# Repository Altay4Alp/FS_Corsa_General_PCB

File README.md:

# Formula Student Corsa Node Board
This is a pcb design for a car we made called Corsa. Corsa is made to create experiences for team to make better cars for formula student races. In this pcb design it is aimed to control the car and getting datas from the car. 

The board designed to use: 
- 3 temprature sensor
- 2 servo motor
- 1 dc motor
- 1 gps sensor
- 1 acceleration sensor
- 1 stop light
- 1 can bus line

That list can be used as a default by just programming. But it is designed to be able to use all of the potential of STM32 blue pill. Sensors and other things can be added as wanted.

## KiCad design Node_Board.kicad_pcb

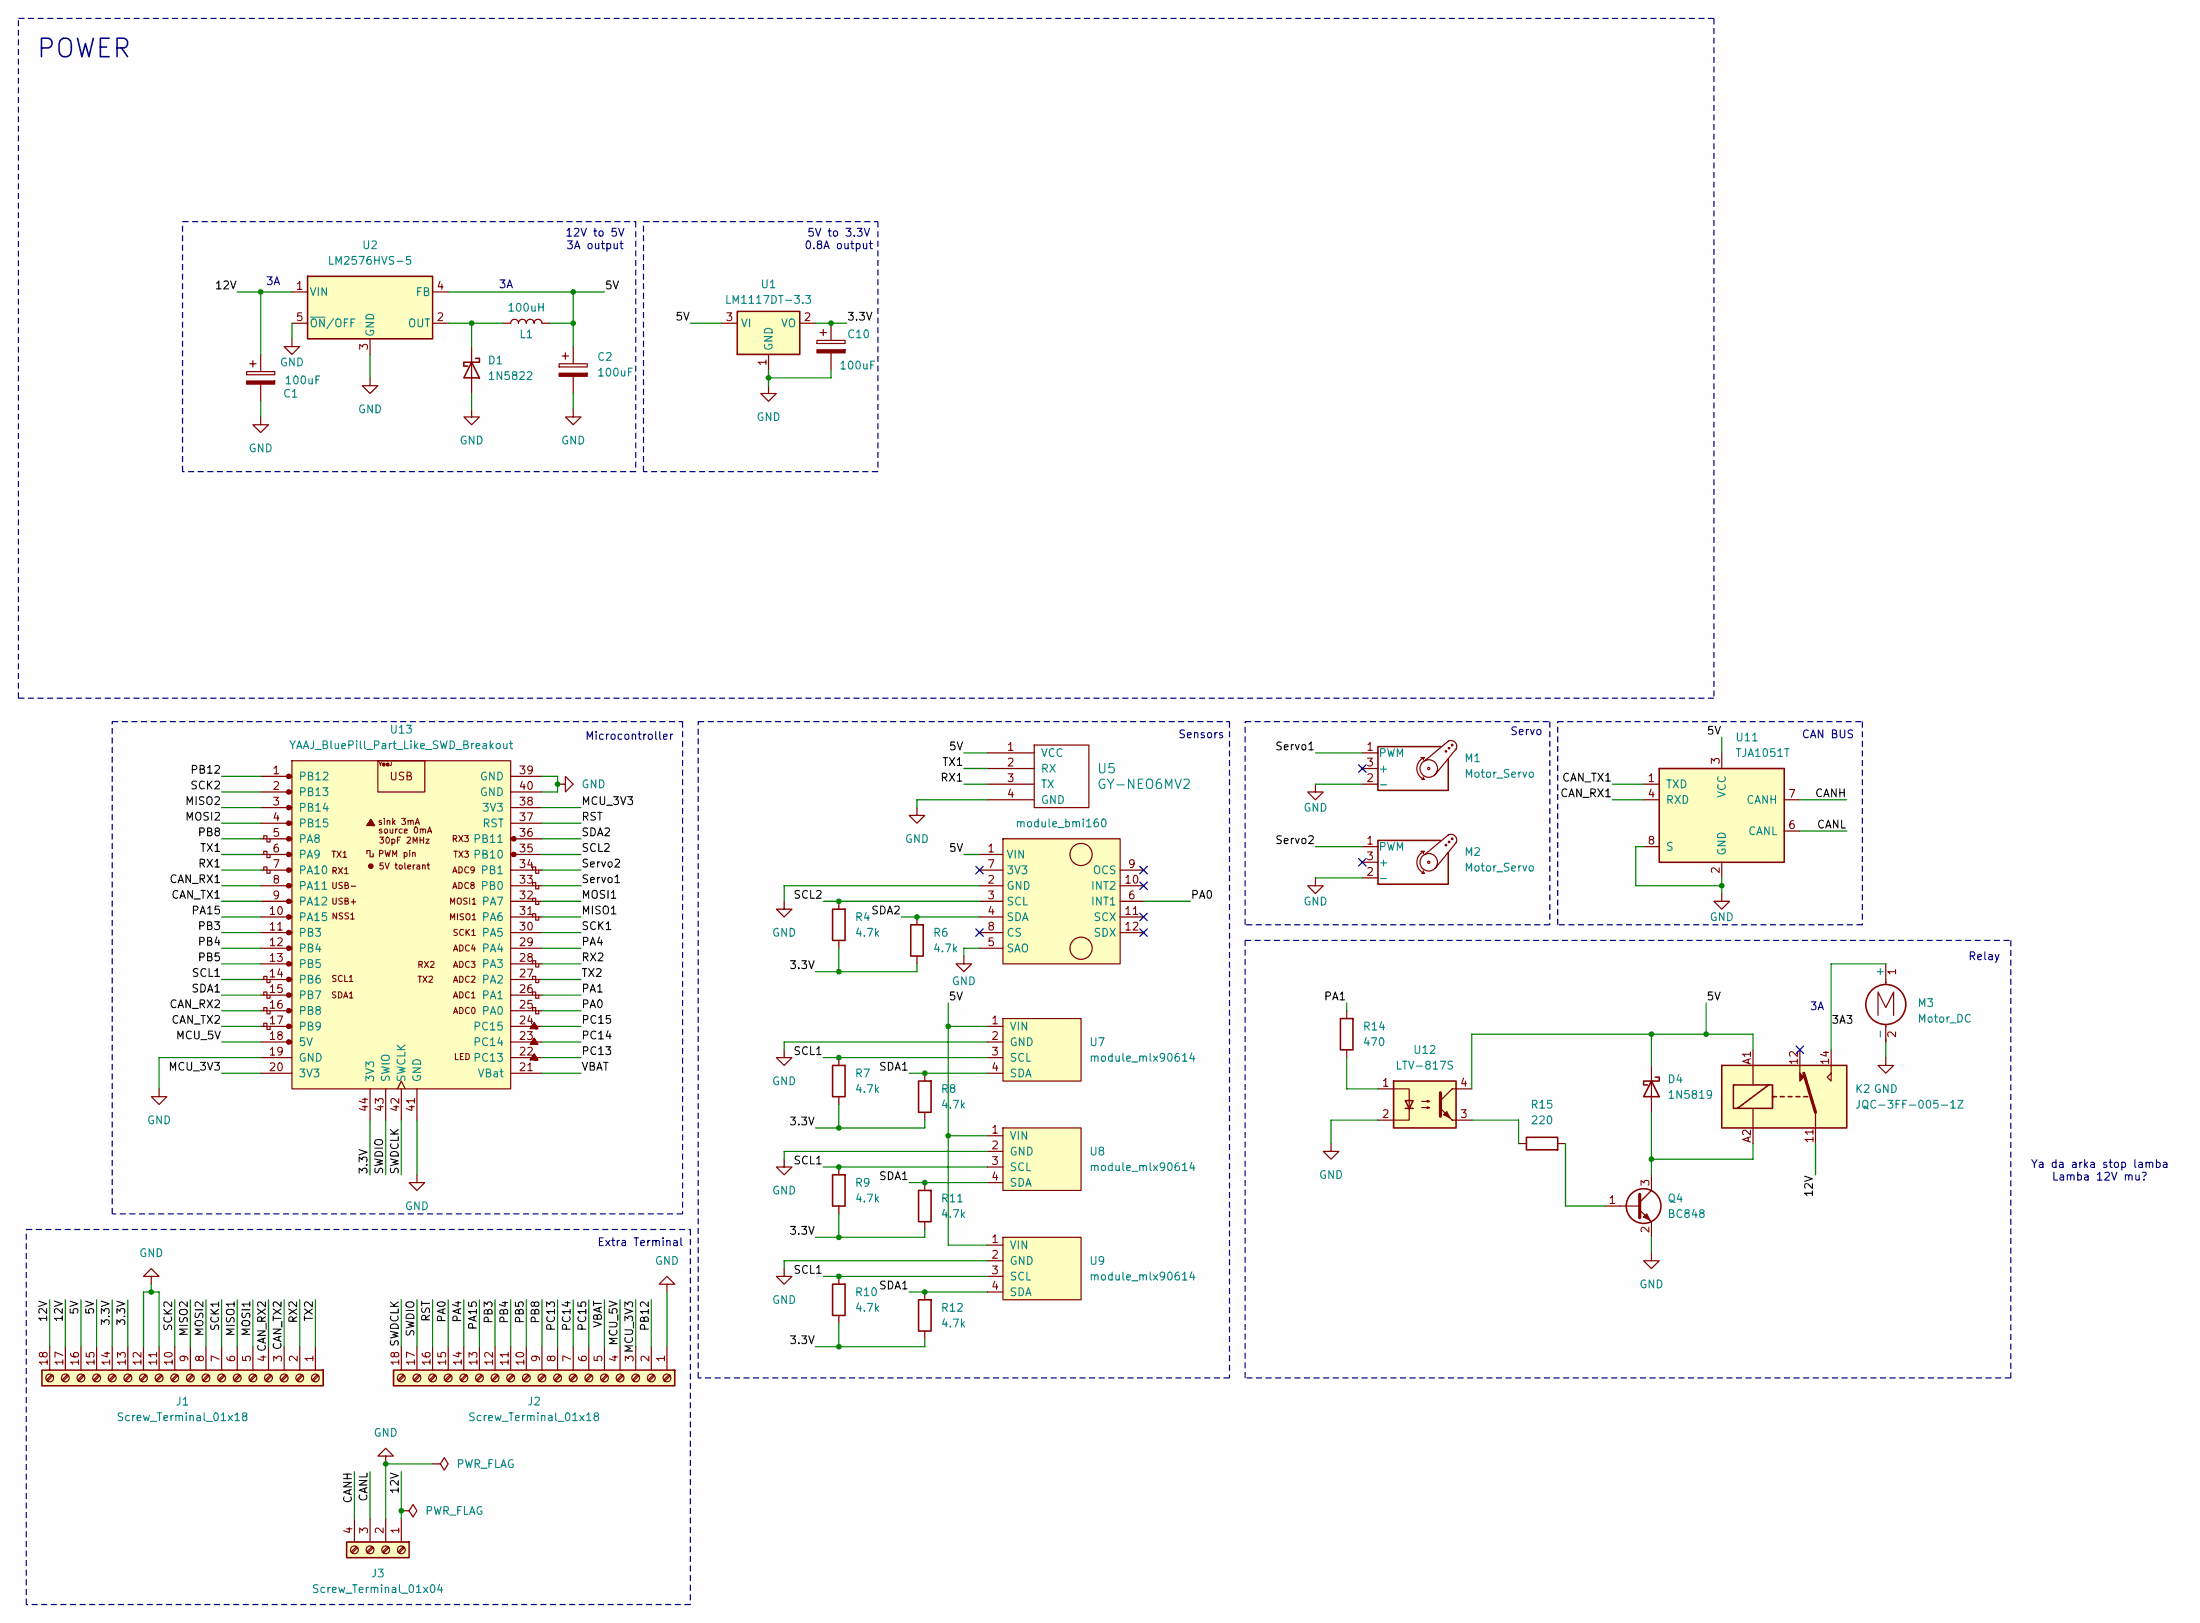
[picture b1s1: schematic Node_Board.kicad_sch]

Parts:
C1, C2: 100uF; CP_Elec_8x10
C10: 100uF; CP_EIA-3528-21_Kemet-B
D1: 1N5822; D_DO-201AD_P15.24mm_Horizontal
D4: 1N5819; D_DO-41_SOD81_P10.16mm_Horizontal
J1, J2: Screw_Terminal_01x18; PinHeader_1x18_P2.54mm_Vertical
J3: Screw_Terminal_01x04; PinHeader_1x04_P2.54mm_Vertical
K2: JQC-3FF-005-1Z; Relay_SPDT_Hongfa_JQC-3FF_0XX-1Z
L1: 100uH; L_12x12mm_H8mm
M1, M2: Motor_Servo; PinHeader_1x02_P2.54mm_Vertical
M3: Motor_DC; PinHeader_1x02_P2.54mm_Vertical
Q4: BC848; SOT-23
R4, R6, R7, R8, R9, R10, R11, R12: 4.7k; R_1206_3216Metric
R14: 470; R_1206_3216Metric
R15: 220; R_1206_3216Metric
U1: LM1117DT-3.3; TO-252-3_TabPin2
U2: LM2576HVS-5; TO-263-5_TabPin3
U5: GY-NEO6MV2; PinHeader_1x04_P2.54mm_Vertical
U7, U8, U9: module_mlx90614; PinHeader_1x04_P2.54mm_Vertical
U10: module_bmi160; PinHeader_1x06_P2.54mm_Vertical
U11: TJA1051T; SOIC-8_3.9x4.9mm_P1.27mm
U12: LTV-817S; SMDIP-4_W9.53mm
U13: YAAJ_BluePill_Part_Like_SWD_Breakout; YAAJ_BluePill_SWD_1

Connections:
/3.3V: C10.1, J1.13, J1.14, R4.1, R6.1, R7.1, R8.1, R9.1, R10.1, R11.1, R12.1, U1.2 (VO), U13.44 (3V3)
/3A3: K2.14, M3.1 (+)
/5V: C2.1, D4.1 (K), J1.15, J1.16, K2.A1, L1.2, U1.3 (VI), U2.4 (FB), U5.1 (VCC), U7.1 (VIN), U8.1 (VIN), U9.1 (VIN), U10.1 (VIN), U11.3 (VCC), U12.4
/12V: C1.1, J1.17, J1.18, J3.1, K2.11, U2.1 (VIN)
/CANH: J3.4, U11.7 (CANH)
/CANL: J3.3, U11.6 (CANL)
/CAN_RX1: U11.4 (RXD), U13.8 (PA11)
/CAN_RX2: J1.4, U13.16 (PB8)
/CAN_TX1: U11.1 (TXD), U13.9 (PA12)
/CAN_TX2: J1.3, U13.17 (PB9)
/MCU_3V3: J2.3, U13.20 (3V3), U13.38 (3V3)
/MCU_5V: J2.4, U13.18 (5V)
/MISO1: J1.6, U13.31 (PA6)
/MISO2: J1.9, U13.3 (PB14)
/MOSI1: J1.5, U13.32 (PA7)
/MOSI2: J1.8, U13.4 (PB15)
/PA0: J2.15, U10.6 (INT1), U13.25 (PA0)
/PA1: R14.2, U13.26 (PA1)
/PA4: J2.14, U13.29 (PA4)
/PA15: J2.13, U13.10 (PA15)
/PB3: J2.12, U13.11 (PB3)
/PB4: J2.11, U13.12 (PB4)
/PB5: J2.10, U13.13 (PB5)
/PB8: J2.9, U13.5 (PA8)
/PB12: J2.2, U13.1 (PB12)
/PC13: J2.8, U13.22 (PC13)
/PC14: J2.7, U13.23 (PC14)
/PC15: J2.6, U13.24 (PC15)
/RST: J2.16, U13.37 (RST)
/RX1: U5.3 (TX), U13.7 (PA10)
/RX2: J1.2, U13.28 (PA3)
/SCK1: J1.7, U13.30 (PA5)
/SCK2: J1.10, U13.2 (PB13)
/SCL1: R7.2, R9.2, R10.2, U7.3 (SCL), U8.3 (SCL), U9.3 (SCL), U13.14 (PB6)
/SCL2: R4.2, U10.3 (SCL), U13.35 (PB10)
/SDA1: R8.2, R11.2, R12.2, U7.4 (SDA), U8.4 (SDA), U9.4 (SDA), U13.15 (PB7)
/SDA2: R6.2, U10.4 (SDA), U13.36 (PB11)
/SWDCLK: J2.18, U13.42 (SWCLK)
/SWDIO: J2.17, U13.43 (SWIO)
/Servo1: M1.1 (PWM), U13.33 (PB0)
/Servo2: M2.1 (PWM), U13.34 (PB1)
/TX1: U5.2 (RX), U13.6 (PA9)
/TX2: J1.1, U13.27 (PA2)
/VBAT: J2.5, U13.21 (VBat)
GND: C1.2, C2.2, C10.2, D1.2 (A), J1.11, J1.12, J2.1, J3.2, M1.2 (-), M2.2 (-), M3.2 (-), Q4.2 (E), U1.1 (GND), U2.3 (GND), U2.5 (~ON/OFF), U5.4 (GND), U7.2 (GND), U8.2 (GND), U9.2 (GND), U10.2 (GND), U10.5 (SAO), U11.2 (GND), U11.8 (S), U12.2, U13.19 (GND), U13.39 (GND), U13.40 (GND), U13.41 (GND)
unnamed: D1.1 (K), L1.1, U2.2 (OUT)
unnamed: D4.2 (A), K2.A2, Q4.3 (C)
unnamed: Q4.1 (B), R15.2
unnamed: R14.1, U12.1
unnamed: R15.1, U12.3

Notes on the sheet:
Sensors
5V to 3.3V 0.8A output
POWER
Ya da arka stop lamba Lamba 12V mu?
Servo
Relay
CAN BUS
Extra Terminal
12V to 5V 3A output
Microcontroller

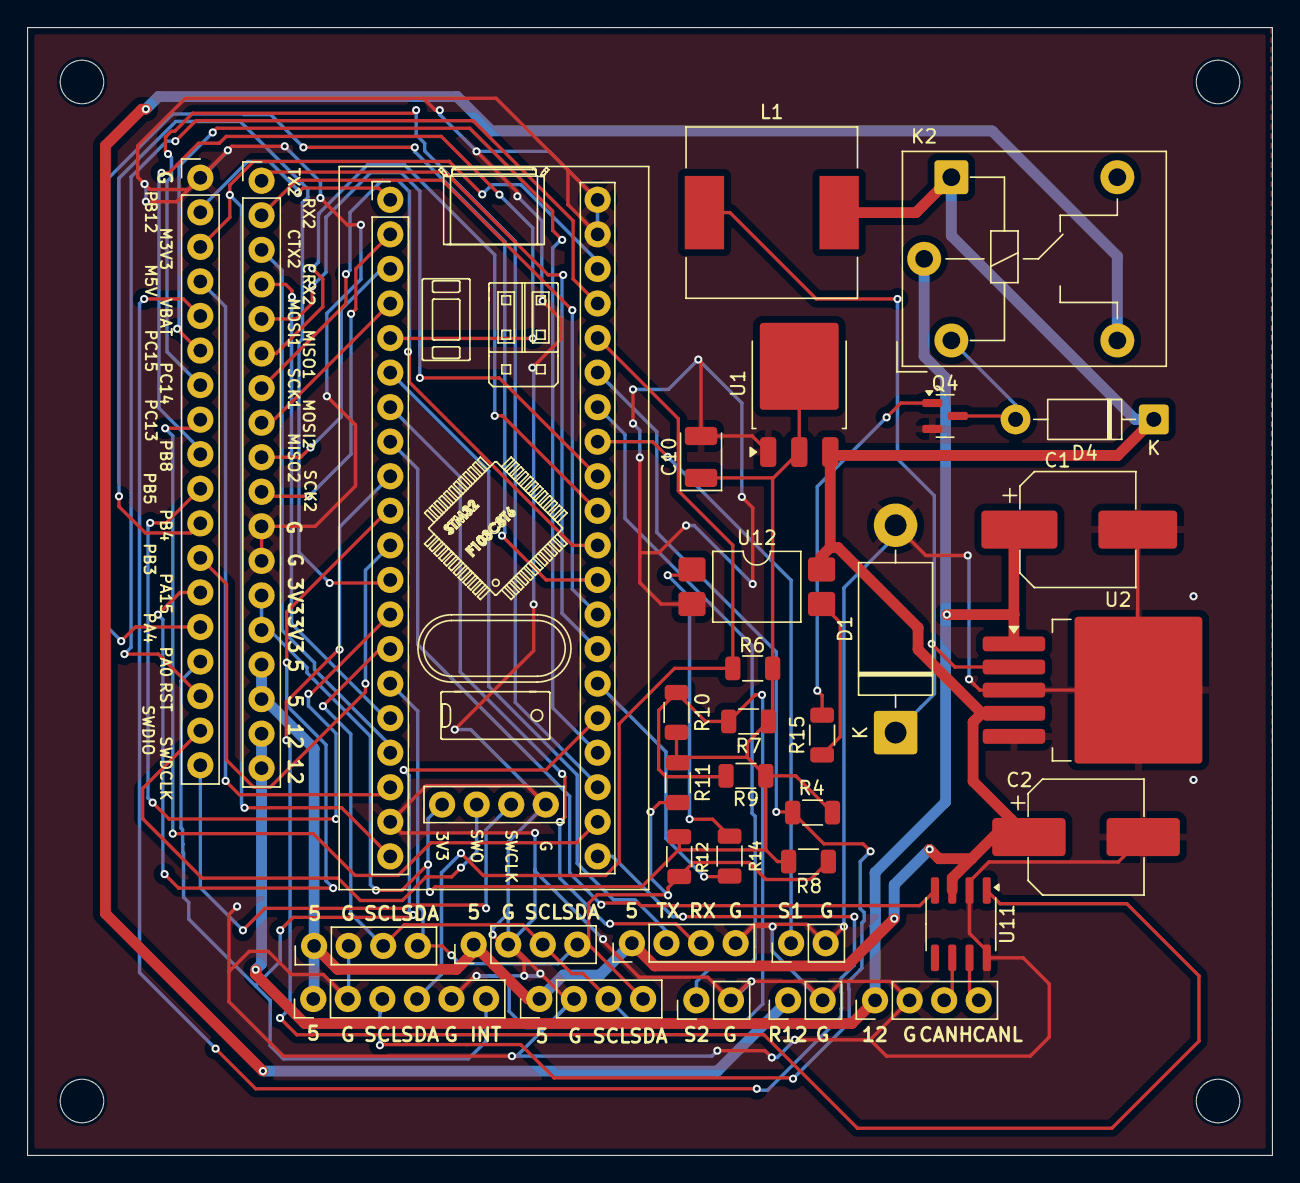
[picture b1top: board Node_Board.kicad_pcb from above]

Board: 2 copper layers, 91.5 x 82.9 mm, 34 parts (0 on the bottom side), 50 nets.

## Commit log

2025-08-12 Update README.md
    General explanation made
2025-08-12 Create Node_Board
2025-08-12 File Changes
2025-08-12 Images
2025-08-12 README.md
